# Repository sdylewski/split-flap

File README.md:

-# Split-Flap
+# Split-Flap
+
(   )
+
+
+
+This fork builds on the brilliant [original project](https://github.com/Dave19171/split-flap) by
+[David Königsmann](https://github.com/Dave19171) and adds a modern web UI, OTA updates,
+message scheduling, a WiFi setup portal, diagnostics and numerous firmware
+improvements while keeping the 3D-printable mechanical design.
+
+## Feature Highlights
+
+- Multi-mode web UI (text, countdown, date, clock) with scheduling and OTA
+- Non-blocking ESPMaster firmware that keeps HTTP requests responsive
+- Built-in WiFi setup portal (AP mode) plus optional static IP/direct mode
+- LED error indicator (ESP-01S), page-load debug logs and copyable serial logs
+- Message splitting for long strings, newline support and REST endpoints
+
+## Documentation
+
+All project documentation now lives under [`docs/`](./docs). Start here:
+
+| Topic | Description |
+| --- | --- |
+| [`docs/README.md`](./docs/README.md) | Docs hub + quick start |
+| [`docs/printing.md`](./docs/printing.md) | BOM, screw list, printed parts, flap tips |
+| [`docs/hardware-build.md`](./docs/hardware-build.md) | PCB soldering, unit assembly, enclosure |
+| [`docs/software.md`](./docs/software.md) | Firmware setup, calibration, debugging, usage |
+| [`docs/SplitFlapInstructions.md`](./docs/SplitFlapInstructions.md) | Legacy PDF converted to Markdown |
+
+## Repository Structure
+
+```
+.
+├── docs/                 # Documentation hub
+├── ESPMaster/            # ESP-01S firmware + web assets
+├── Unit/                 # Arduino Nano unit firmware
+├── EEPROM_Write_Offset/  # Utility sketch for per-unit offsets
+├── PCB/                  # Schematics, Gerbers, pick-and-place
+├── Images/               # Reference photos used in docs
+└── Instructions/         # Original PDF (kept for reference)
+```
+
+## Getting Started
+
+1. Review [`docs/printing.md`](./docs/printing.md) to print and source parts
+2. Follow [`docs/hardware-build.md`](./docs/hardware-build.md) to assemble the
+   PCBs, units and enclosure
+3. Configure firmware, calibrate offsets and explore the web UI using
+   [`docs/software.md`](./docs/software.md)
+
+Have improvements or fixes? Contributions are welcome—open an issue or a pull
+request and help the display flip even better!

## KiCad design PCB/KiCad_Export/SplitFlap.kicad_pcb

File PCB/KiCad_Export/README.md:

# KiCad Project - Split Flap Display PCB

This directory contains the KiCad project files converted from EasyEDA source files.

## Files

- `SplitFlap.kicad_pro` - Main KiCad project file
- `SplitFlap.kicad_sch` - Schematic file
- `SplitFlap.kicad_pcb` - PCB layout file
- `SplitFlap.kicad_sym` - Symbol library
- `EasyEDA.pretty/` - Footprint library directory

## Opening in KiCad

1. **Install KiCad 6.x or later** (required for these files)
   - Download from: https://www.kicad.org/download/

2. **Open the project:**
   - Launch KiCad
   - File → Open Project
   - Navigate to this directory and open `SplitFlap.kicad_pro`

3. **Add libraries (if needed):**
   - The footprint library `EasyEDA.pretty` should be automatically detected
   - If not, go to Preferences → Manage Footprint Libraries → Project Specific Libraries
   - Add the `EasyEDA.pretty` directory

## Assigning 3D Models to Components

To get a complete 3D STEP file with all components, you need to assign 3D models to each footprint. The components are already placed on the PCB, but their 3D models need to be linked.

### Method 1: Using KiCad's 3D Viewer (Recommended)

1. **Open the PCB Editor:**
   - In KiCad, click on the PCB Editor icon or open `SplitFlap.kicad_pcb`

2. **View in 3D:**
   - Click the **3D Viewer** button (or View → 3D Viewer)
   - This shows which components have 3D models and which don't

3. **Assign 3D Models to Footprints:**
   - Right-click on a component footprint → **Properties**
   - Click the **3D Models** tab
   - Click **Add 3D Model**
   - Browse to find the 3D model file (`.step`, `.wrl`, or `.obj` format)
   - Adjust position/rotation if needed
   - Click **OK**

4. **Download 3D Models:**
   - **GrabCAD**: https://grabcad.com/library (search by part number)
   - **3D ContentCentral**: https://www.3dcontentcentral.com/
   - **SnapEDA**: https://www.snapeda.com/ (free account required)
   - **KiCad 3D Model Library**: Check if models exist in KiCad's default library
   - **Component Manufacturers**: Many provide STEP files on their websites

### Method 2: Batch Assign Using Footprint Editor

1. **Open Footprint Editor:**
   - Tools → Footprint Editor

2. **Edit Each Footprint:**
   - File → Open Footprint
   - Navigate to `EasyEDA.pretty/` and open the footprint
   - Click the **3D Models** tab
   - Add the 3D model file
   - Save the footprint

3. **Update PCB:**
   - The changes will automatically apply to all instances of that footprint on the PCB

### Method 3: Using EasyEDA Component Library (if available)

The converter may have created references to 3D models. Check if they exist:
- Look in the footprint files in `EasyEDA.pretty/` for 3D model references
- The converter creates references like: `${KICAD6_3DMODEL_DIR}/EasyEDA.3dshapes/footprint_name.wrl`
- You may need to download these models from EasyEDA/LCSC or find equivalent models

## Exporting 3D STEP File

Once 3D models are assigned:

1. **Open the PCB Editor:**
   - In KiCad, click on the PCB Editor icon or open `SplitFlap.kicad_pcb`

2. **Verify 3D Models:**
   - Open 3D Viewer (View → 3D Viewer)
   - Check that components show 3D models (not just flat pads)
   - If components appear flat, they need 3D models assigned

3. **Export STEP file:**
   - Go to **File → Export → STEP...**
   - Choose a location and filename (e.g., `SplitFlap_PCB.step`)
   - **Important**: Check the options:
     - ✅ Include 3D models for components
     - ✅ Include board outline
   - Click **Save**

4. **The STEP file will include:**
   - PCB board outline
   - All component footprints positioned correctly
   - 3D models of components (if assigned)

## Key Components on This PCB

Based on the BOM, main components include:
- **ULN2003A** (U4) - DIP-16 package - Common 3D models available
- **L7805CV** (U3) - TO-220 package - Standard regulator, models widely available
- **AMS1117-3.3** (U9) - SOT-223 package - Common LDO, models available
- **Arduino Nano** (U1) - Custom footprint - May need custom model or approximate
- **ESP-01S** (U2) - Custom WiFi module - May need custom model
- **JST Connectors** (U6, U7, U8, U10) - XH series - Models available from JST
- **DIP Switch** (SW1) - Custom footprint - May need approximate model
- **Passive components** (C0805, R0805, etc.) - Standard SMD - Models widely available

### Quick Tips for Finding 3D Models:

1. **Standard packages** (0805, SOT-23, TO-220, etc.):
   - Search by package name on GrabCAD or 3D ContentCentral
   - KiCad's default library may have some

2. **Specific parts** (ULN2003A, L7805CV):
   - Search by part number on manufacturer websites
   - Many have STEP files in their product pages

3. **Custom parts** (Arduino Nano, ESP-01S):
   - Arduino: Official Arduino website or GrabCAD
   - ESP-01S: Ai-Thinker website or approximate with similar ESP module models

4. **Connectors** (JST XH series):
   - JST provides 3D models on their website
   - Search "JST XH 3D model STEP"

## Notes

- The conversion created 3 messages during PCB conversion - check the User.Cmts layer in the PCB editor for details
- Some manual adjustments may be needed for component 3D models
- Components are already placed on the PCB from the EasyEDA conversion
- You only need to assign 3D models - the physical placement is already correct
- The original EasyEDA source files are in `../EasyEDA_Source/`

## Original Source Files

- PCB: `../EasyEDA_Source/PCB_PCB_Splitflap_2022-06-04.json`
- Schematic: `../EasyEDA_Source/SCH_SplitFlap_2022-06-04.json`
- BOM: `../BOM_PCB_Splitflap_2022-03-11.csv`

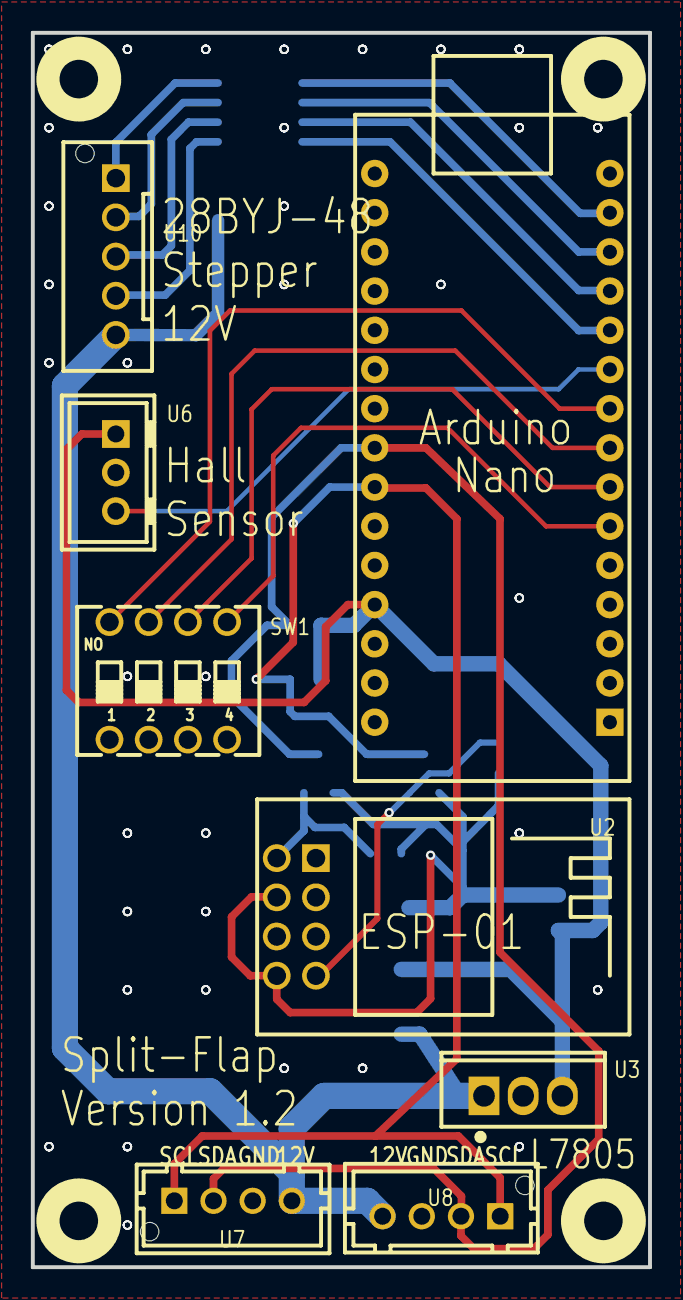
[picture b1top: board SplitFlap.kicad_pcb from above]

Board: 2 copper layers, 40.0 x 80.0 mm, 48 parts (0 on the bottom side), 21 nets.

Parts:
C1: 330nF; C0805
C2: 100nF; C0805
C5: 22μF; CAP-SMD_L3.2-W1.6
Q1, Q2: BSS138; SOT-23-3_L2.9-W1.3-P1.90-LS2.4-BR
R1, R2, R3, R4: 10K; R0805
SW1: DSWB04LHGET; SW-TH_DSWB04LHGET
U2: ESP-01S; WIFIM-TH_ESP-01S
U3: L7805CV; TO-220-3_L10.0-W4.5-P2.54-L
U4: ULN2003A; SOP-16_L10.0-W3.9-P1.27-LS6.0-BL
U6: B3B-XH-A(LF)(SN); CONN-TH_3P-P2.50_B3B-XH-A-LF-SN
U7, U8: B4B-XH-AM(LF)(SN); CONN-TH_B4B-XH-AM-LF-SN
U9: AMS1117-3.3; SOT-223-3_L6.5-W3.4-P2.30-LS7.0-BR
U10: B5B-XH-AM (LF)(SN); CONN-TH_B5B-XH-AM-LF-SN
gge2518: hole_0.91_mm; TH_pad_gge2518
gge2533: hole_0.91_mm; TH_pad_gge2533
gge2548: hole_0.91_mm; TH_pad_gge2548
gge2563: hole_0.91_mm; TH_pad_gge2563
gge2578: hole_0.91_mm; TH_pad_gge2578
gge2596: hole_0.91_mm; TH_pad_gge2596
gge2611: hole_0.91_mm; TH_pad_gge2611
gge2626: hole_0.91_mm; TH_pad_gge2626
gge2641: hole_0.91_mm; TH_pad_gge2641
gge2656: hole_0.91_mm; TH_pad_gge2656
gge2674: hole_0.91_mm; TH_pad_gge2674
gge2689: hole_0.91_mm; TH_pad_gge2689
gge2707: hole_0.91_mm; TH_pad_gge2707
gge2722: hole_0.91_mm; TH_pad_gge2722
gge2737: hole_0.91_mm; TH_pad_gge2737
gge2752: hole_0.91_mm; TH_pad_gge2752
gge2767: hole_0.91_mm; TH_pad_gge2767
gge2782: hole_0.91_mm; TH_pad_gge2782
gge2797: hole_0.91_mm; TH_pad_gge2797
gge2812: hole_0.91_mm; TH_pad_gge2812
gge2827: hole_0.91_mm; TH_pad_gge2827
gge2845: hole_0.91_mm; TH_pad_gge2845
gge2860: hole_0.91_mm; TH_pad_gge2860
gge2875: hole_0.91_mm; TH_pad_gge2875
gge2890: hole_0.91_mm; TH_pad_gge2890
gge2905: hole_0.91_mm; TH_pad_gge2905
gge2920: hole_0.91_mm; TH_pad_gge2920
gge2935: hole_0.91_mm; TH_pad_gge2935
gge2950: hole_0.91_mm; TH_pad_gge2950
gge2968: hole_0.91_mm; TH_pad_gge2968

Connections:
+3.3V: C5.1, Q1.1, Q2.1, R1.2, R3.2, U2.5, U2.7, U9.2, U9.4
+5V: C2.1, R2.2, R4.2, U3.3, U6.1, U9.3, gge2797.1
GND: C1.2, C2.2, C5.2, SW1.5, SW1.6, SW1.7, SW1.8, U2.1, U3.2, U4.8, U6.2, U7.3, U8.3, U9.1, gge2563.1, gge2767.1
Q1_2: Q1.2, R1.1, U2.4
Q2_2: Q2.2, R3.1, U2.8
U1_6: SW1.4, gge2596.1
U1_7: SW1.3, gge2611.1
U1_8: SW1.2, gge2626.1
U1_9: SW1.1, gge2641.1
U1_10: U6.3, gge2656.1
U1_11: U4.4, gge2674.1
U1_12: U4.3, gge2689.1
U1_13: U4.2, gge2707.1
U1_14: U4.1, gge2722.1
U1_23: Q2.3, R4.1, U7.2, U8.2, gge2860.1
U1_24: Q1.3, R2.1, U7.1, U8.1, gge2845.1
U4_13: U4.13, U10.4
U4_14: U4.14, U10.3
U4_15: U4.15, U10.2
U4_16: U4.16, U10.1
VCC: C1.1, U3.1, U4.9, U7.4, U8.4, U10.5

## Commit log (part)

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2021-09-09 Added DHCP Hostname
    Makes it easier to find IP on router.
2021-09-11 ezTime library time handling
    The split flap now uses the ezTime for all the time and date handling. Time and date format is now easily customizable.
    Thanks to Sergio for the great suggestion!
2021-12-19 fixed test routine
    moved test routine from loop to setup. This way the sleep routine does not interfere.
2022-01-02 fixed wrong datatype
2022-03-11 Create BOM_PCB_Splitflap_2022-03-11.csv
    added BOM
2022-06-04 add EasyEDA PCB Source files
2022-12-30 added Instructions to github
2023-06-13 Update FlapFunctions.ino
    fixed "control reaches end of non-void function" error due to closed off return in if in function
2023-06-13 type comparisons mismatch fix
    Fixed error: comparison of integer expressions of different signedness
2023-08-31 Updated string alignment methods
    - Left align string clears off any text to the right
    - Right align string implementation added
    - Center string when provided a long string, then subsequently a short string, did not clear the right hand side of the string
2023-09-12 Add Arduino libraries into repo
    Added the libraries/dependencies to repository in case cannot access again later
2023-09-12 Added driver for Arduino use with windows
2023-09-12 Refactor and revise ESPMaster implementation
    - Updated naming conventions throughout the application and 'data' folder
    - Added functionality to be able to use "Scheduled Messages"
    - Reworked the UI
    - Added ability to see things like, amount of units, message last received, version
    - Updated layout
    - Added ability to send scheduled messages
2023-09-12 Updated readme with extra guidance and information
2023-11-28 Remove "beta" from the version
2023-11-28 Updated README.md with more details: - Corrected typos - Added missing "LinkedList" library - Some extra details for setup
2023-11-30 Updated LittleFS plugin zip as was missing some content
2023-11-30 Rename the "Unit.ino" file
2023-11-30 Added links to reboot and ota on the main page
2023-11-30 Several fixes and improvements - Changes to OTA to try make it work a little better - Updated docs - Improve reboot
2023-12-19 Remove duplicate version number (sorry!)
2023-12-19 Added multiple driver versions for use on Windows
2023-12-19 Added a "Reset Units" method
2023-12-19 Added a simple reset button to UI
2023-12-20 Added a basic recalibration function to the UI
    This code will simply cycle the flaps to do a full rotation which
    triggers a calibration for the units. It should return to what was being
    done prior to the recalibration
2024-01-14 Feature: GitHub Action Build (#2)
    * Create CI builds for all the Arduino sketches
    * Create build badges
2024-01-19 Feature: Countdown and WiFi Manager Functionality (#3)
    * Worked on UI to add some quality of life improvements
    * Time Zone offset is now returned from the server for settings
    * Refactoring the codebase to be more readable
    * Introduce WiFiManager
    * Remove redundant service time functions file
    * Move countdown and schedule message logic into separate files
2024-01-31 Update README.md
    Corrected the screenshot for the AP being inline with the text
2024-02-07 Small README improvements
2024-03-03 Added to README user proposed solution
2024-03-03 Corrected user link in README
2024-03-10 Feature: Removal of zip dependencies (#4)
    * Update to remove need for using zip libraries included in library
    * Update README with newer instructions and type correction
    * Update build for GitHub action
    * Update dependencies
2024-03-10 Increase version number to 2.1.0 for ESP Master
2024-04-18 Feature: Indefinite scheduled messages and WiFi Static IP Address (#9)
    * Added functionality for making a message displayed on a schedule permanent
    * Fixed issue where WiFi direct mode did not work correctly
    * Fixed issue with TimeZone being set on the UI
    * Added experimental feature for setting a static IP address
    * Updated build dependencies
    * README updates
2024-04-27 added serial input and calibration via serial support to unit firmware
2024-04-27 store strings in progmem where appropriate
2024-04-27 ESP Master: added support for our modified PCB
2024-04-27 ESP Master: fixed POST data handling to not use unset values
2025-11-25 Added lots of debugging, and it works now!
2025-11-25 Update logging and debug. Seems to be working well.
2025-11-27 Major updates to support new Arduino version.
2025-11-28 Working version. Adding new calibration routine.
2025-12-01 Latest updates
2025-12-11 Update Unit and InteractiveCalibration firmware to version 1.2.0 and 1.0.21 respectively. Implemented forward-only rotation in Unit.ino to prevent mechanical issues and updated calibration logic to s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
2025-12-22 Fix web server startup blocking and add unit testing interface
    - Remove blocking I2C scans and calibration wait from startup to allow immediate web server response
    - Add unit testing table on main page with individual unit test buttons
    - Simplify debug page to just show status and continue button
    - Add I2C diagnostic and setup scan services (ServiceI2CDiagnostics.ino, ServiceI2CSetupScan.ino)
    - Add on-demand I2C scan button on main page
    - Update documentation for LittleFS upload instructions
2025-12-23 update for new Arduino version > 2
2025-12-24 Working version! queries work, and fixes for interactive calibration.
2025-12-29 train station functions and more.
